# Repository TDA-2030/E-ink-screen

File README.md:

# hanshow E-ink example based on ESP32

An assistant to help you view text and picture calendars. It is mainly composed of a 2.13 inch eink(epaper) and an esp32 module.

[ESP32](https://www.espressif.com/zh-hans/products/socs/esp32) of espressif is used as the controller, and development environment is [esp-idf v4.0](https://github.com/espressif/esp-idf/tree/release/v4.0).

## How to Use

1. setup environment

   [ESP-IDF Programming Guide](https://docs.espressif.com/projects/esp-idf/en/latest/esp32/get-started/index.html#installation-step-by-step) will teach you to install the development environment step by step.

2. config project

   open the menuconfig

   ```shell
   cd firmware
   idf.py menuconfig
   ```

    Here you can configure the project. For example, you can change the GPIO of the screen by entering `component config → Eink setting ` .

3. compile project

   ```shell
   idf.py build
   ```

4. download firmware

   ```shell
   idf.py -b 921600 flash monitor
   ```

   The above command will flash esp32 and open a serial monitor to show the logs of esp32.

## File Structure

```shell
.
├── datasheet  #related documents
├── firmware   #firmware of esp32
├── hardware   #PCB project of KiCAD
├── LICENSE
├── README.md
└── tools
```

## Hardware

### Resource on board

- ESP32-WROOM module
- Audio PA，can be input by PWM or DAC
- Type-C for battery charge and download firmware to ESP32
- Design of power supply with complete shutdown

### Known issues of hardware

[hardware\bugfix.md](hardware/bugfix.md)

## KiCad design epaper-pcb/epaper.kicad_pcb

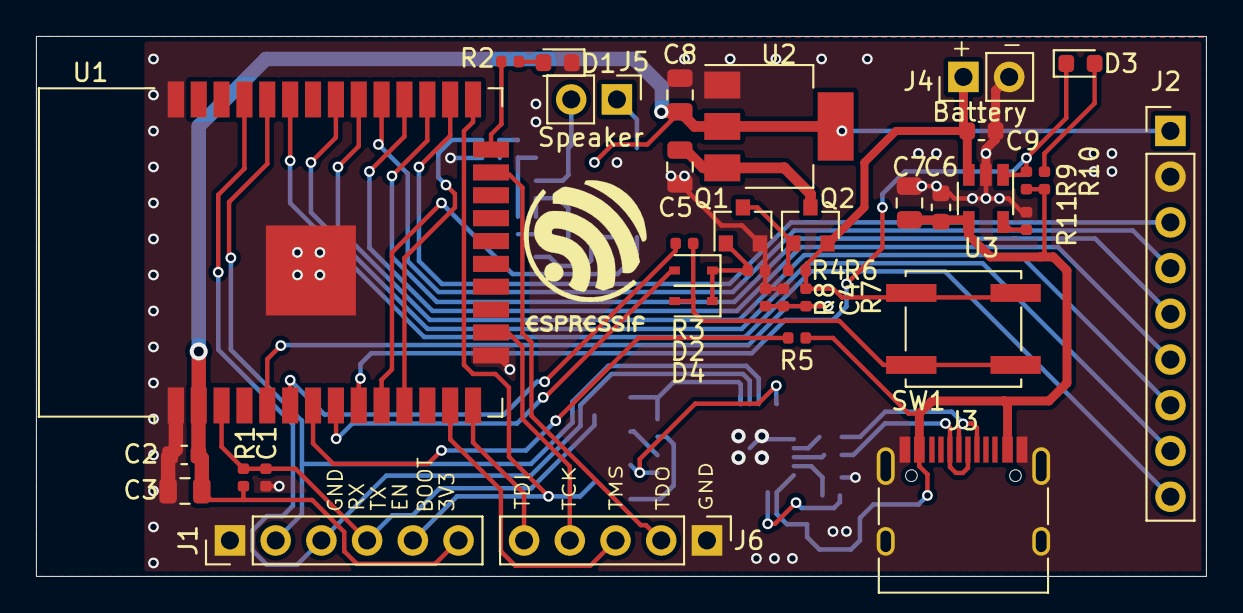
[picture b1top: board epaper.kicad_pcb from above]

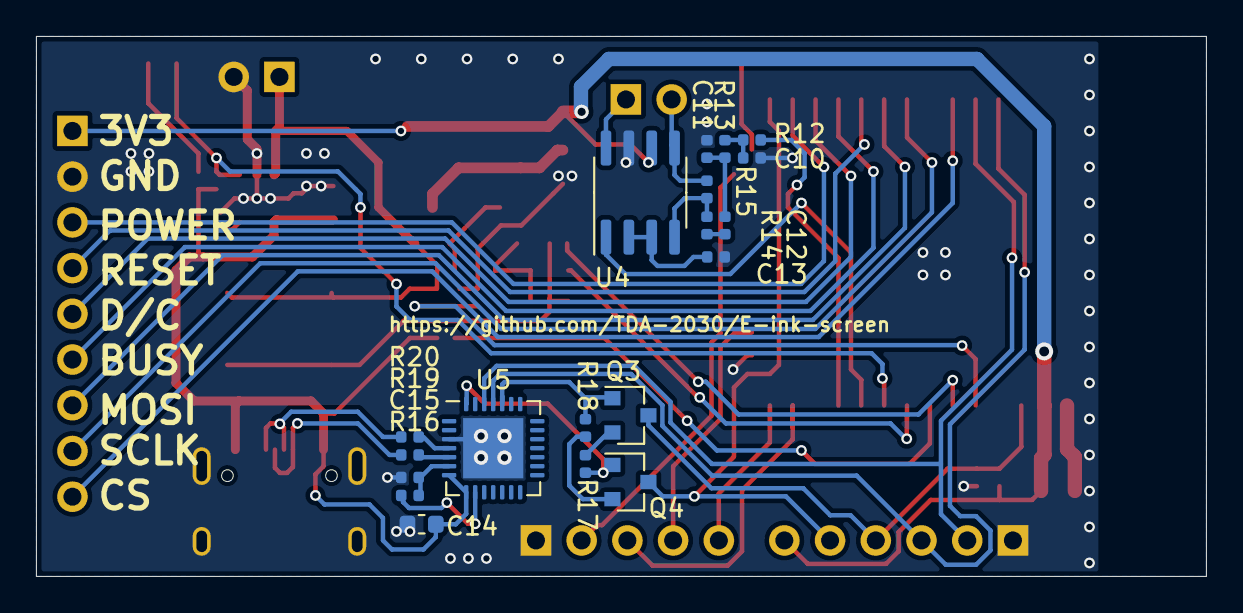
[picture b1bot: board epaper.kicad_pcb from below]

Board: 2 copper layers, 65.0 x 30.0 mm, 55 parts (19 on the bottom side), 51 nets.

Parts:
C1, C4, C15: 0.1uf; C_0402_1005Metric
C2, C6, C9, C14: 1uf; C_0603_1608Metric
C3, C5, C7, C8: 10uf; C_0805_2012Metric
C10, C11, C12: 0.39uf; C_0402_1005Metric
C13: 1uf; C_0402_1005Metric
D1: LED_BLUE; LED_0603_1608Metric
D2, D4: 1N4148WS; D_SOD-323
D3: LED_RED; LED_0603_1608Metric
J1: download; PinHeader_1x06_P2.54mm_Vertical
J2: epaper; PinHeader_1x09_P2.54mm_Vertical
J3: USB_C_Receptacle_USB2.0; USB_C_Receptacle_HRO_TYPE-C-31-M-12
J4: BATT; PinHeader_1x02_P2.54mm_Vertical
J5: Speaker; PinHeader_1x02_P2.54mm_Vertical
J6: JTAG; PinHeader_1x05_P2.54mm_Vertical
Q1: DMG3404L; SOT-23
Q2: AO3401A; SOT-23
Q3, Q4: S8050; SOT-23
R1, R4, R6, R7, R8, R9, R16, R17, R18: 10K; R_0402_1005Metric
R2, R3, R5: 4.7K; R_0402_1005Metric
R10: 1K; R_0402_1005Metric
R11: 1.5K; R_0402_1005Metric
R12, R13, R14, R15: 20k; R_0402_1005Metric
R19, R20: 22; R_0402_1005Metric
SW1: SW_Push; SW_Push_1P1T_NO_CK_KSC7xxJ
U1: ESP32-WROOM-32D; ESP32-WROOM-32
U2: AMS1117-3.3; SOT-223-3_TabPin2
U3: LTC4054ES5-4.2; TSOT-23-5
U4: TC8002D; SOIC-8_3.9x4.9mm_P1.27mm
U5: CP2102N-A01-GQFN28; QFN-28-1EP_5x5mm_P0.5mm_EP3.35x3.35mm

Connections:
+3V3: C2.1, C3.1, C8.1, J1.6, J2.1, R1.1, U1.2, U2.2, U4.6
+5V: C6.2, C7.2, C14.1, J3.A4, J3.A9, J3.B4, J3.B9, R5.2, R9.2, R10.2, U3.4, U5.7, U5.8
+BATT: C9.1, J4.1, Q2.2, R6.1, R7.2, SW1.2, U3.3
/ADC_VOL: C4.1, R7.1, R8.2, U1.5
/BOOT: J1.5, Q4.3, U1.25
/BUSY: J2.6, U1.28
/CS: J2.9, U1.33
/DC: J2.5, U1.27
/EN: C1.1, J1.4, Q3.3, R1.2, U1.3
/MOSI: J2.7, U1.30
/POWER: J2.3, U1.26
/RESET: J2.4, U1.29
/RXD0: J1.2, U1.34, U5.26
/SCLK: J2.8, U1.31
/Sheet5F4ECFED/BUTTON: R3.2, U1.6
/Sheet5F4ECFED/CHRG_STATE: D3.1, R9.1, U1.9, U3.1
/Sheet5F4ECFED/ENABLE: D2.2, U1.8
/Sheet5F4ECFED/USB_CHECK: R5.1, U1.7
/Sheet5F555EA7/INPUT: R12.2, U1.11
/Sheet5F555EA7/SHUTDOWN: U1.10, U4.1
/TCK: J6.4, U1.16
/TDI: J6.5, U1.14
/TDO: J6.2, U1.23
/TMS: J6.3, U1.13
/TXD0: J1.3, U1.35, U5.25
GND: C1.2, C2.2, C3.2, C4.2, C5.2, C6.1, C7.1, C8.2, C9.2, C10.1, C11.1, C13.2, C14.2, C15.1, D1.1, J1.1, J2.2, J3.A1, J3.A12, J3.B1, J3.B12, J3.S1, J4.2, J6.1, Q1.2, R4.1, R8.1, R11.1, U1.1, U1.15, U1.38, U1.39, U2.1, U3.2, U4.7, U5.3, U5.29
unnamed: C5.1, Q2.3, U2.3
unnamed: C10.2, R12.1, R13.2
unnamed: C11.2, C12.2, R13.1
unnamed: C12.1, R14.2
unnamed: C13.1, U4.2, U4.3
unnamed: C15.2, R16.2, U5.6
unnamed: D1.2, R2.1
unnamed: D2.1, D4.1, Q1.1, R4.2
unnamed: D3.2, R10.1
unnamed: D4.2, R3.1, SW1.1
unnamed: J3.A6, J3.B6, R20.2
unnamed: J3.A7, J3.B7, R19.2
unnamed: J5.1, U4.8
unnamed: J5.2, R15.1, U4.5
unnamed: Q1.3, Q2.1, R6.2
unnamed: Q3.1, R18.2, U5.24
unnamed: Q3.2, R17.1
unnamed: Q4.1, R17.2, U5.28
unnamed: Q4.2, R18.1
unnamed: R2.2, U1.24
unnamed: R11.2, U3.5
unnamed: R14.1, R15.2, U4.4
unnamed: R16.1, U5.9
unnamed: R19.1, U5.5
unnamed: R20.1, U5.4

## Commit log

2020-08-27 add code files
2020-08-29 fix(edp2in13): add timeout
2020-08-29 refactor: tjpgd
2020-08-29 feat: add web configure
2020-08-29 feat: add sntp for clock
2020-08-29 feat: add web file server
2020-08-29 add pic
2020-08-29 fix: add diagnostics color
2020-08-29 fix(picture): compilation failed issue
2020-08-29 feat(edp2in13): add kconfig
2020-08-29 fix(file_server): add cpp condition
2020-08-30 feat(edp2in13): add draw image api
2020-08-30 feat(picture): add dynamic alloc memory
2020-08-30 fix(main): change to C++
    add two dithering process for images
2020-08-30 fix: remove redundant config options from main/Kconfig.projbuild
2020-08-30 fix: Adapting code to C++
2020-08-30 refactor: put pretty process into pretty_effect.c
2020-08-30 fix(file_server): webpage table size
2020-08-30 feat(file_server): add creat_file_table api
2020-08-30 fix(pretty_effect): add function declaration
2020-08-30 test(main): test file_server new api
2020-08-30 fix(main): modify image size lead to decoder memory leak
2020-08-31 pcb: add schematic files
2020-09-01 feat: add image show function
2020-09-02 feat(pcb): add pcb design
2020-09-03 feat(pcb): add pcb line design
2020-09-05 feat(pcb): compeleted pcb line design
2020-09-06 refactor: adjust file structure
2020-09-06 feat: add text show
2020-09-06 fix: modify default edpio config to adapt pcb
2020-09-06 feat: add PCB 3D rendering resource
2020-09-10 feat: add show text
2020-09-20 feat(components): add multibutton
2020-09-25 fix(webpage_config): set wifi storage to flash
2020-09-25 fix(mian): add spiffs_create_partition_image
2020-09-26 fix(main): add board.c to control peripheral on board like button led
2020-09-26 fix(epd2in13): add API Epd_Set_LUT
2020-09-26 fix(MultiButton): modify LONG_TICKS to 10 second
2020-09-26 hardware: add case model for 3D printer
2020-09-26 feat: add mp3 player function
2020-09-26 fix(epd2in13): replace c++ code with c
2020-09-26 fix(webpage_config): add param configured into captive_portal_start
2020-09-26 fix(main): add ssid info display when starting
2020-09-26 hardware: add file bugfix.md
2020-09-26 feat(main): add power off action with double click button
2020-09-26 feat(adc_audio): add api adc_audio_set_volume
2020-10-15 fix(pwm_audio): fix abnormal of pwm_audio
2020-10-17 feat(epd2in13): add GDEH0213B72 screen
2020-10-18 fix: restore cmakelist.txt and modify show image interval
2020-10-18 fix(epd2in13): fix epaper driver
2020-10-18 docs: update readme.md
2020-10-18 hardware: update bugfix.md
2020-10-18 docs: add GDEH0213B72 screen and controller datasheet
2020-11-07 chore: add tools folder
2020-11-07 fix(firmware): modify partition table
2024-12-02 update for support esp32-c6 board
